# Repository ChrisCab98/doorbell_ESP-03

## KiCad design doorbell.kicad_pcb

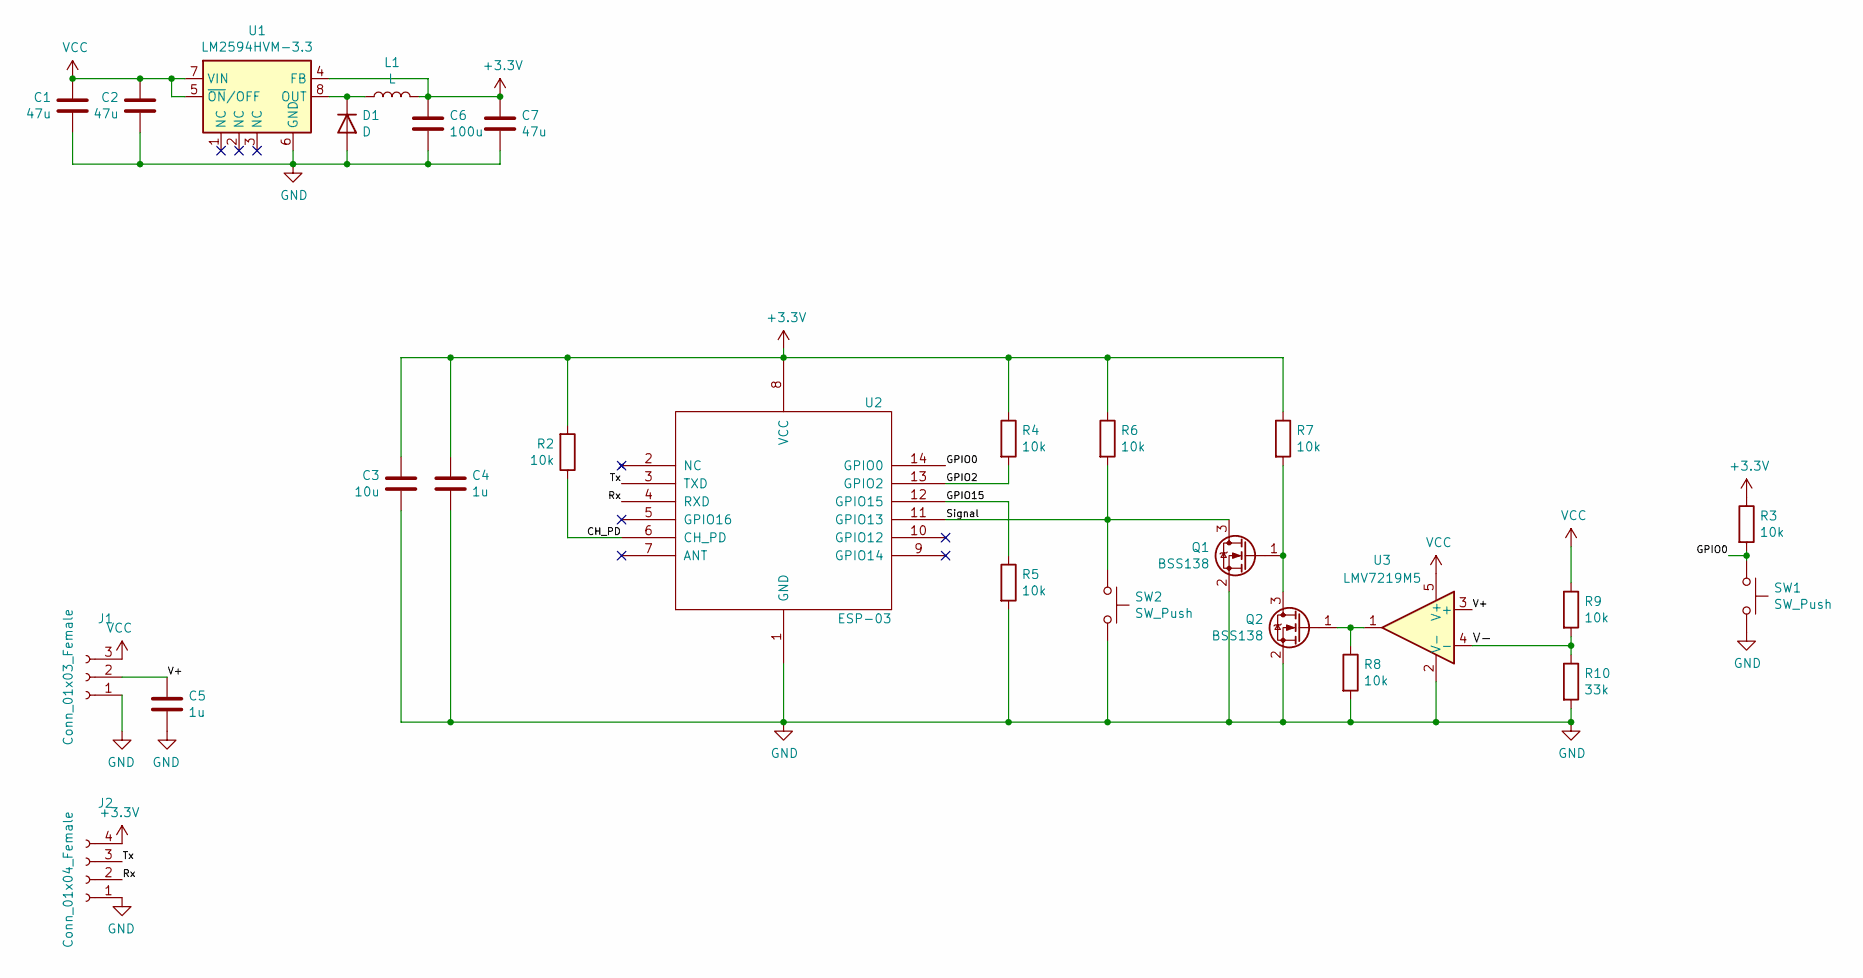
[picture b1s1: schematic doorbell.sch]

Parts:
C1, C2, C7: 47u; C_1210_3225Metric_Pad1.42x2.65mm_HandSolder
C3: 10u; C_0603_1608Metric_Pad1.05x0.95mm_HandSolder
C4, C5: 1u; C_0603_1608Metric_Pad1.05x0.95mm_HandSolder
C6: 100u; C_1210_3225Metric_Pad1.42x2.65mm_HandSolder
D1: D; D_0603_1608Metric_Castellated
J1: Conn_01x03_Female; PinHeader_1x03_P2.54mm_Vertical
J2: Conn_01x04_Female; PinHeader_1x04_P2.54mm_Vertical
L1: L; Wuerth_Elektronik-7447714101-Manufacturer_Recommended
Q1, Q2: BSS138; SOT-23_Handsoldering
R2: 10k; R_0603_1608Metric
R3, R4, R5, R6, R7, R8, R9: 10k; R_0603_1608Metric_Pad1.05x0.95mm_HandSolder
R10: 33k; R_0603_1608Metric_Pad1.05x0.95mm_HandSolder
SW1, SW2: SW_Push; SW_SPST_PTS810
U1: LM2594HVM-3.3; SOIC-8_3.9x4.9mm_P1.27mm
U2: ESP-03
U3: LMV7219M5; SOT-23-5

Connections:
+3V3: C3.1, C4.1, C6.1, C7.1, J2.4, L1.2, R2.2, R3.1, R4.1, R6.1, R7.1, U1.4 (FB), U2.8 (VCC)
/CH_PD: R2.1, U2.6 (CH_PD)
/GPIO0: R3.2, SW1.1, U2.14 (GPIO0)
/GPIO2: R4.2, U2.13 (GPIO2)
/GPIO15: R5.1, U2.12 (GPIO15)
/Rx: J2.2, U2.4 (RXD)
/Signal: Q1.3 (D), R6.2, SW2.1, U2.11 (GPIO13)
/Tx: J2.3, U2.3 (TXD)
/V+: C5.1, J1.2, U3.3 (+)
/V-: R9.2, R10.1, U3.4 (-)
GND: C1.2, C2.2, C3.2, C4.2, C5.2, C6.2, C7.2, D1.2 (A), J1.1, J2.1, Q1.2 (S), Q2.2 (S), R5.2, R8.2, R10.2, SW1.2, SW2.2, U1.6 (GND), U2.1 (GND), U3.2 (V-)
unnamed: D1.1 (K), L1.1, U1.8 (OUT)
unnamed: Q1.1 (G), Q2.3 (D), R7.2
unnamed: Q2.1 (G), R8.1, U3.1
VCC: C1.1, C2.1, J1.3, R9.1, U1.5 (~ON~/OFF), U1.7 (VIN), U3.5 (V+)

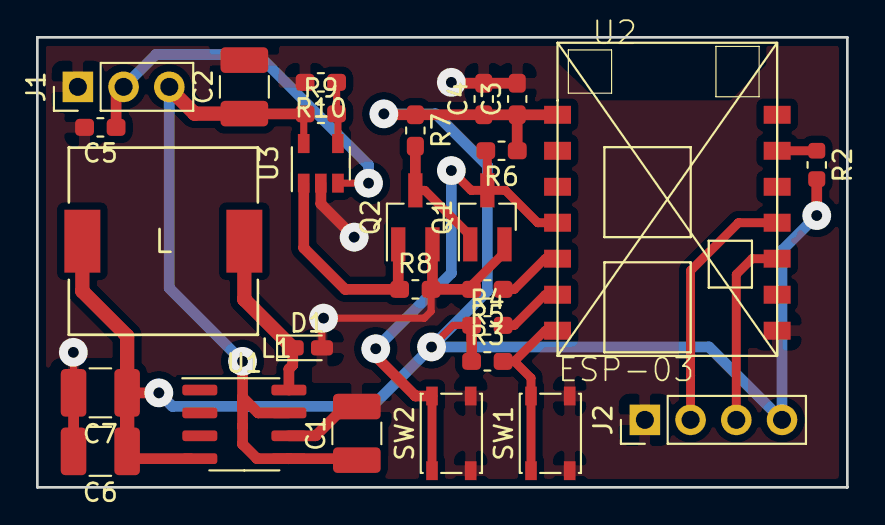
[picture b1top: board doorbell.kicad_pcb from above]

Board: 2 copper layers, 45.0 x 25.0 mm, 27 parts (0 on the bottom side), 15 nets.

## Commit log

2021-08-11 SMPS Version
